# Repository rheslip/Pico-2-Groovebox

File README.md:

# Pico 2 Groovebox
 Sample player/groovebox based on RP2350

Oct 2025 - added step editor and .stl files for 3D printed enclosure. SD interface changed from SPI to SDIO which improved flie loading speed a lot. Tweeks to the sensitivity of some of the MPR121 keypad keys have been added. I had issues with keypresses being detected too easily or not at all. Still not completely resolved but much improved. Various other bug fixes and enhancements.

demo and tutorial https://www.youtube.com/watch?v=hEJh2LgJkRc&t=5s 

**Hardware components used**

Pimoroni Pico 2+ with 8mb PSRAM (for sample storage)

Generic PCM5102A DAC module from AliExpress

160x128 ST7735 color TFT display

Encoder with switch

24 pad touch keyboard PCB - gerbers are in the hardware directory. $4 including shipping for 5 PCBs from JLCPCB.com

2x MPR121 touch sensor modules from AliExpress

Micro SD breakout board **Note that the latest version of the code uses SDIO which is much faster**

**Optional:**

LiPo battery - I used 1500mah for approx 8 hours use

LiPo charger module from AliExpress

Power switch

3V to 5V stepup regulator from AliExpress

3d Printed Case - .stl files in the hardware section. Design is for a build on 80x120mm perfboard available on Aliexpress or Amazon. No doubt will need tweeking unless your layout is exactly like mine.

There is no schematic but it should be pretty obvious how to wire the modules to the RP2350 board if you look at IO.h in the source code.

**Overview**

Pico 2 Groovebox is a flexible sample player + groovebox with 16 tracks and 16 scenes. Samples can be oneshots or loops. You can play samples with the keypad, play loops, record clips and use drum trigger patterns. Each track has a sequencer which triggers a sample to play. Sequences can be from 1 to 128 steps but normally you would set tracks up as multiples of 16 steps (1 bar). 

It is helpful to think of tracks and scenes as a matrix with columns as tracks and rows as scenes. This setup is similar to Ableton and most grooveboxes. You can record a clip in every cell of this 16x16 matrix ie up to 144 clips, subject to memory limitation which is currently 512 total notes per track. 

The basic workflow is to select a track by holding the TRACK key and select the track using the number pads. Use the Track menus to load a .WAV file sample to a track from the SD card - this saves it in PSRAM for playback (SD is way too slow for direct playback). You can then record a clip (a sequence of sample triggers) by tapping the REC key and touching the the numbered keypads. Holding the REC key will erase the sequence. To change tracks hold the TRACK key and select another track using the number pads.

You can record up to 16 clips per track. Clips are organized by scenes ie rows of clips. Hold the SCENE key to select a scene using the number pads. Selecting a scene will launch all clips on that row of the clip matrix.

Tap the PLAY button to start or stop playback of all clips in the current scene. Hold the PLAY button to start playback in Song mode (described below).

When the sequencers are running you can play samples using the keypad to jam over the current scene, record sequences while the scene is playing, switch scenes and even record in song mode. 

Internally, clips are stored as MIDI sequences. I may consider adding MIDI I/O to the Pico 2 Groovebox so it could be used as a 16 channel MIDI recorder/sequencer.

**Track Screen and Menus**

The top line of the screen shows the currently selected Track:Scene, Song and Record indicators when enabled, and a Bar:Step indicator. On the far right is a simple battery level display.

Below that is a sequencer progress bar which indicates where the sequencer is. This is helpful when recording.

Below the progress bar is a small piano roll display showing the notes recorded on the track. If random velocities are enabled (see below) the color of the steps will range from Magenta (low velocity) to Red (highest velocities).

Below the piano roll is a parameter menu for each track for loading a sample, setting the track length in steps, setting the volume and pan, adjusting the tuning of the sample, adjusting the track shuffle timing, enabling or disabling sample slicing, and to adjust the pattern generator parameters.

**Setup Menu**

Hold the TRACK key and turn the encoder to scroll through tracks 1-16. The first menu past track 16 is the Song chain menu (below). The next menu is Setup which allows selection of BPM, master volume and the musical scale to use on the numbered keys.

**Scales**

There are currently ten musical scales to select from. Selecting a scale changes the layout of the numbered keys. Key 9 plays the sample at its nominal pitch. Playing keys above key 9 will raise the pitch of the sample according to the selected scale. e.g. if the selected scale is chromatic each numbered key above 9 increases the pitch by one semitone. Likewise, keys below 9 reduce the pitch according to the selected scale.

Note that sample pitch and sample tuning are accomplished by a resampling algorithm so higher pitches will play for a shorter time and lower pitches become longer in duration. ie no timestretching going on here!

**Pattern Generator**

The pattern generator is an alternate way of loading trigger patterns into the sequencer. There are currently fifty three 16 bit trigger patterns organized from fewest triggers with pattern 0 having no triggers to pattern 53 which triggers on every sequencer step. Trigger patterns include some common drum patterns and some Euclidean patterns. If the sequencer length is longer than 16, the pattern will be repeated till the sequencer is full. If the sequencer length is less than 16 the trigger pattern will be shortened to the sequencer length. This is a handy way to chop a pattern off - shorten the sequence, load a trigger pattern and then lengthen the sequence.

The Pattern Shift parameter shifts the trigger pattern right one bit at a time, adding 16 more patterns to each of the basic trigger patterns.

The Pattern Offset parameter generates a series of random pitch offsets in the range selected in the menu. These offsets are added to the base note of the sample, quantized to the current scale and inserted into the sequencer. This results in a random melody in the current scale using the current pattern. 

The Level Offset parameter generates a series of random velocity offsets in the range selected in the menu. These offsets are added to velocity of the sample to give the sequence some random volume variations. The Level Offset parameter is scaled such that its maximum value (16) results in a random velocity range of 0 to 127.

The Autorandomizer parameter when "On" will re-randomize the pitch offsets and velocity offsets when the sequencer loops back to the first step. Huge fun when used with the sample slicer on loops!

Note that the pattern generator overwrites the sequencer clip with a new generated sequence when any of its parameters are changed. This means you can record more steps over a pattern but you can't add a pattern on top of a recorded clip.

**Step Editor**

The pattern step editor is accessed by pressing the F1 key - "Edit" will appear at the top of the display. A green cursor will appear under the first step on the piano roll. The number to the right of "Edit" is the step the cursor is on - rotate the encoder to change steps. To edit a step press the encoder - the cursor will turn red indicating we are entering or editing a note at this step. If there is no note at the step one will automatically be inserted with MIDI note 60 - the MIDI note number appears beside the step number at the top of the screen. Turn the encoder to change the note pitch (+-1 octave). To remove a note, turn the encoder until the note dissappears off the top or bottom of the piano roll display. Press the encoder to exit note entry mode. Press F1 again to exit the step editor. 

**Clip/Scene Cut and Paste**

To copy a clip, press the Copy key while that clip is on the screen. Select a different clip (using Track and or Scene keys as above) and press the Paste key to copy the sequence to that clip.

To copy an entire scene, hold the Scene key and press the Copy key to copy the current scene. Select a new scene using the Scene key and the numbered keys and press Paste to paste into the new scene.

**Sample Slicer**

The Slices parameter in the track menu controls if slicing is off (slices=0) or the number of uniform sample slices to use up to a maximum of 16. Sample slices are mapped to the numbered keys - if the number of slices is less than 16 the slice pattern repeats over the numbered keys. Slices can be played on the keypad, recorded as a clip or sequenced with the pattern generator. If using the pattern generator, the Sample Offset is used to select which sample is played on active sequencer steps. ie if Sample Offset is 0, the pattern will only include the first slice, if Sample Offset is 1 it will randomly include slice 0 or slice 1 etc.

Sample Slicer + Pattern Generator Autorandomizer = a lot of fun! 

**Song Chain**

As described above, the first menu when scrolling past track 16 is the Song Chain. The Song Chain is a list of scenes and the number of repeats for each  scene. By default all scene counts are 0 except for Scene 1 which will always have a minimum repeat count of 1. A song chain is set up by selecting the number of times you would like each scene to repeat. If the count is 0, that scene is skipped. At the the end of the chain the song will restart at Scene 1. To play the song, hold the Play key until the "SONG" indicator on the top line of the display is on. To turn song mode off, hold the Play key until the "SONG" indicator goes off.

Note: In song mode, a scene is completed/counted down when ALL clips arrive on the last step at the same time. e.g. if one of the tracks is set to a sequence length of 64 and the others are 16 steps, the other tracks will be repeated 4 times and when the 64 step sequence ends the scene counter will be counted down. If we have a track with a sequence length of 16 and another with a length of 15, it will take 16 iterations for the two tracks to arrive at the last step at the same time. If you add another track with 14 steps, its going to take a long time for them to all arrive at the last step at the same time! In general you should keep sequence lengths multiples of 16 or 1 bar.

**A Word on SD Cards**

I don't think its mandatory for micro SD card to work with a SPI interface. I have a small assortment of 4gb, 8gb and 16gb micro SD cards and very few of them seem to work with SPI. **Note that the latest version of the code uses SDIO to access the SD card**. Make sure the card is formatted as FAT16 or FAT32. All samples **MUST** be under a directory in the root named "Samples". As mentioned before it is suggested you organize your samples in subdirectories with no more than 50 or so samples to keep loading time to a minimum. The maximum path length is 200 characters so don't go too crazy on the directory and sample name lengths.

**FAQ**

How do you compile the source? I used arduino 2.3.2 with Arduino Pico v 4.1. You will need Adafruit graphics library, the ST 7735 driver, and probably some other libs I've forgotten. The rest of the stuff is in the source tree. I started with the Adafruit FifteenStep MIDI recorder library but I had to modify it a lot so I renamed it SixteenStep and its included in the library directory.

Why not have sequencer length set up in bars? I debated this and actually had it set up with bars at one point. I opted for the flexibility of having sequences be any length (up to 128). Its useful for ambient stuff or jamming when you want things to sound similar but not repeat exactly. Set two drum tracks to different lengths for example and the rhythm will change as the beats change relative to each other on every loop.

Why the pattern generator? I had it set up as just a recorder and then quickly realized its hard (for me anyway) to play the pads to record exactly on step 1, which you want if you have multiple scenes (so scene changes are in sync). The pattern generator makes it easy to place triggers where you want them and relative to each other.

Is the code stable? Not completely. It crashes now and then but I've used it for hours on end with no glitches. Still working on those pesky bugs...

Why is loading files so slow? **Its MUCH better with the new SDIO interface**. Still not as fast as I'd like but very usable.

What file formats will it read? 16 and 24 bit, 44hkz, 22khz, stereo or mono .WAV files. It converts everything to 22khz mono internally. I suggest you organize your samples into directories with no more than 50 or so samples per directory to minimize loading time.

Why do you use 22khz mono internally? To minimize memory use. With 8mbytes RAM you can load about 190 seconds of 22khz mono samples vs only 47 seconds with 44khz stereo. Use the pan control for fake stereo - it actually sounds really good even at 22khz.

Why don't you do a PCB? It would probably have to be two boards to work mechanically. I'm not that great at PCB layout - maybe somebody else would take this on if I do a schematic in Kicad?

What are the F1 and F2 keys for? TBD. I'm thinking of adding some more features like track mute and solo

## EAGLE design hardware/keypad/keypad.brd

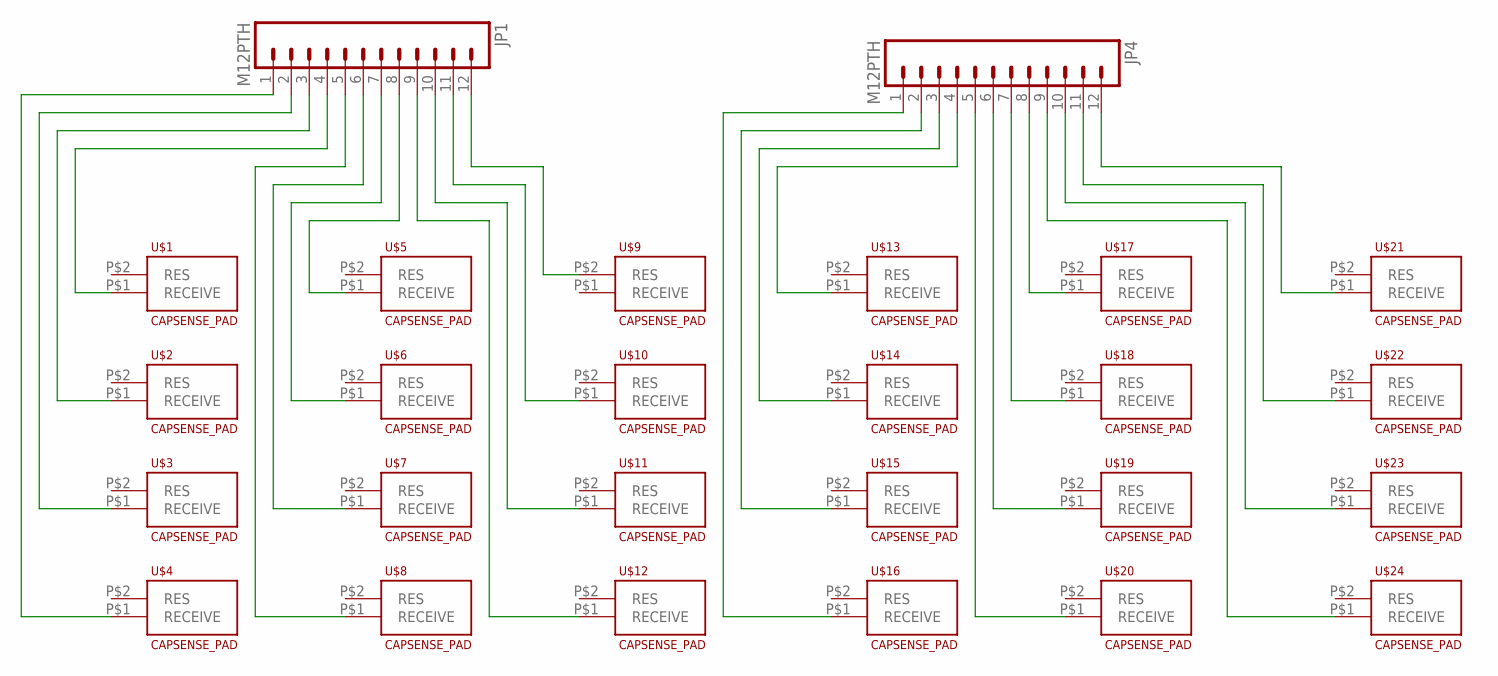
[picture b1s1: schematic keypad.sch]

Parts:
JP1, JP4: M12PTH; 1X12
U$1, U$2, U$3, U$4, U$5, U$6, U$7, U$8, U$9, U$10, U$11, U$12, U$13, U$14, U$15, U$16, U$17, U$18, U$19, U$20, U$21, U$22, U$23, U$24: CAPSENSE_PAD

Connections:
unnamed: JP1.1, U$4.P$1 (RECEIVE)
unnamed: JP1.2, U$3.P$1 (RECEIVE)
unnamed: JP1.3, U$2.P$1 (RECEIVE)
unnamed: JP1.4, U$1.P$1 (RECEIVE)
unnamed: JP1.5, U$8.P$1 (RECEIVE)
unnamed: JP1.6, U$7.P$1 (RECEIVE)
unnamed: JP1.7, U$6.P$1 (RECEIVE)
unnamed: JP1.8, U$5.P$1 (RECEIVE)
unnamed: JP1.9, U$12.P$1 (RECEIVE)
unnamed: JP1.10, U$11.P$1 (RECEIVE)
unnamed: JP1.11, U$10.P$1 (RECEIVE)
unnamed: JP1.12, U$9.P$2 (RES)
unnamed: JP4.1, U$16.P$1 (RECEIVE)
unnamed: JP4.2, U$15.P$1 (RECEIVE)
unnamed: JP4.3, U$14.P$1 (RECEIVE)
unnamed: JP4.4, U$13.P$1 (RECEIVE)
unnamed: JP4.5, U$20.P$1 (RECEIVE)
unnamed: JP4.6, U$19.P$1 (RECEIVE)
unnamed: JP4.7, U$18.P$1 (RECEIVE)
unnamed: JP4.8, U$17.P$1 (RECEIVE)
unnamed: JP4.9, U$24.P$1 (RECEIVE)
unnamed: JP4.10, U$23.P$1 (RECEIVE)
unnamed: JP4.11, U$22.P$1 (RECEIVE)
unnamed: JP4.12, U$21.P$1 (RECEIVE)

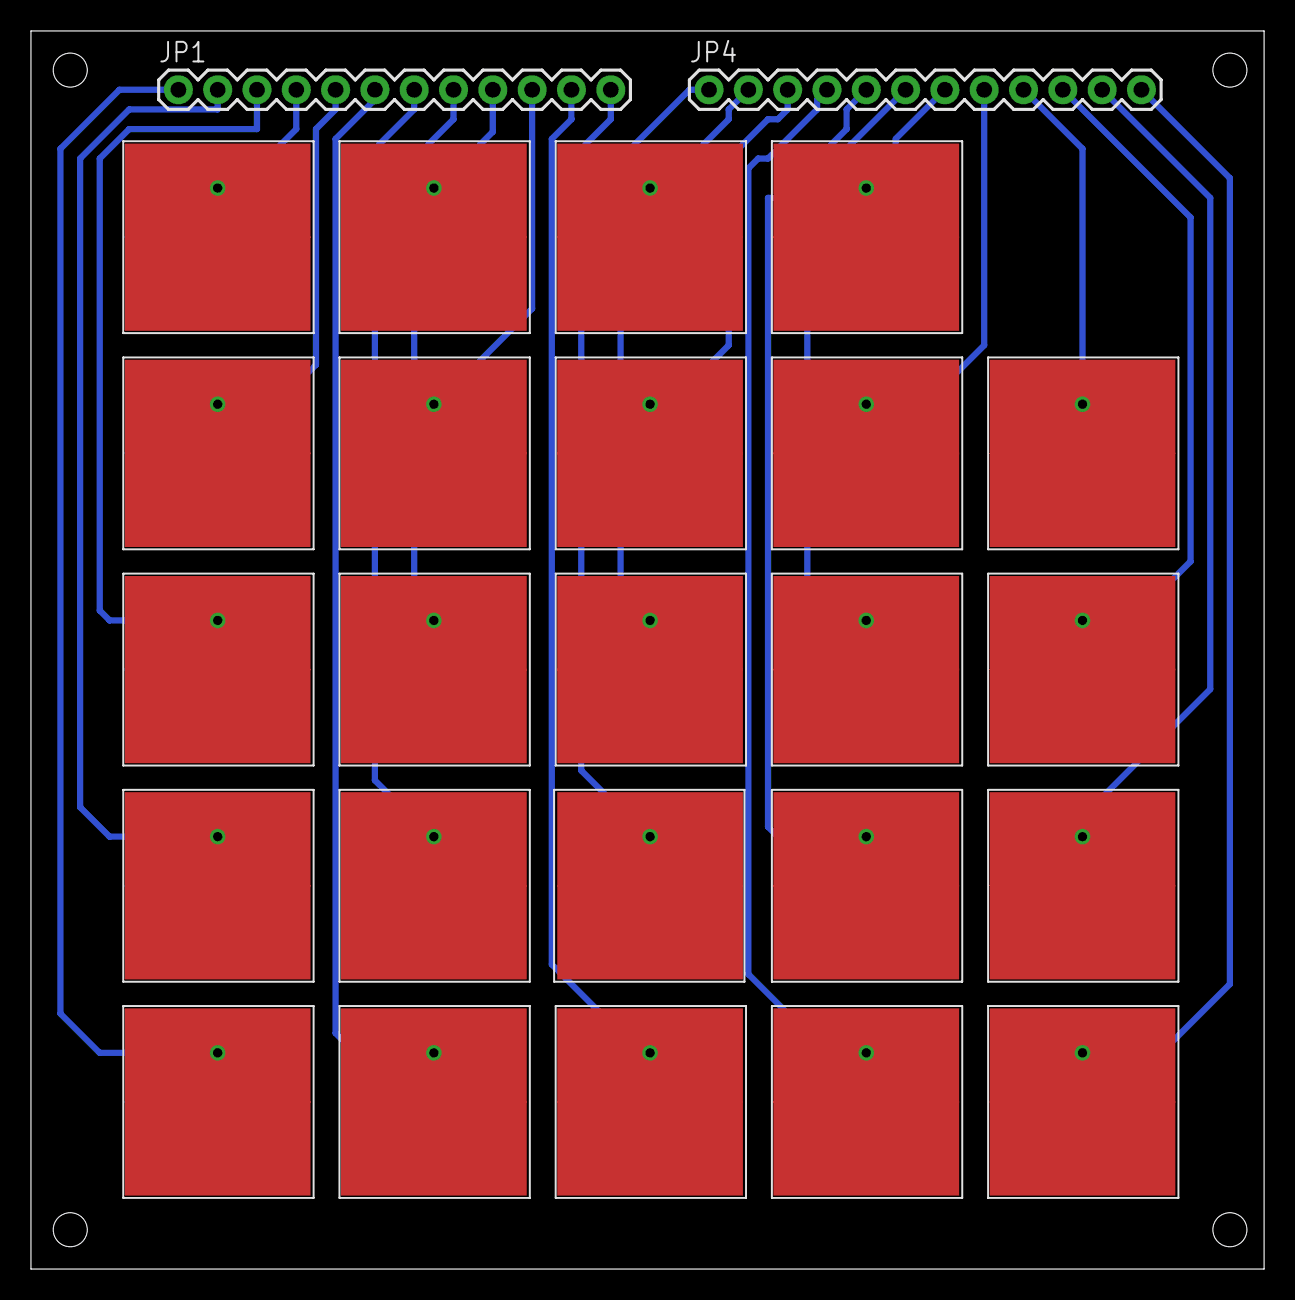
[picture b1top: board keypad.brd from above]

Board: 2 copper layers, 79.7 x 80.0 mm, 26 parts (0 on the bottom side), 24 nets.

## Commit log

2024-10-27 Initial commit
    Groovebox based on RP2350
2024-10-28 Update Readme
    Updated Readme with basic instructions
2024-10-28 Update README.md
    updated readme
2024-10-28 Updated readme
    Updated readme and added some images
2024-11-04 Fixed .wav loader, added autorandomizer
    Fixed crash loading to .wav files, added autorandomizer feature
2024-11-07 Added Step Editor
    Added a step editor. F1 key to enter/exit editor. Turn encoder to change step, press encoder to toggle step editing
2024-11-08 Tweeks to editor
    To delete a note now you scroll past the top or below the bottom of the note range. There are a few clicks of deadzone now instead of just 1.
2025-10-07 SDIO and 3D printed enclosure, step editor
    This version has switched the SD card interface to SDIO for speed. stl files for a 3D printed enclosure are included. A step editor has been added to the software along with a lot of other fixes and 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
2025-10-07 Update README.md
    Update readme

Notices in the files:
parts and their libraries:
SparkFun-Connectors: Licensing: Creative Commons ShareAlike 4.0 International - https://creativecommons.org/licenses/by-sa/4.0
